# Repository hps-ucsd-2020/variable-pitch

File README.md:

# variable-pitch

This is where code for the variable pitch system goes

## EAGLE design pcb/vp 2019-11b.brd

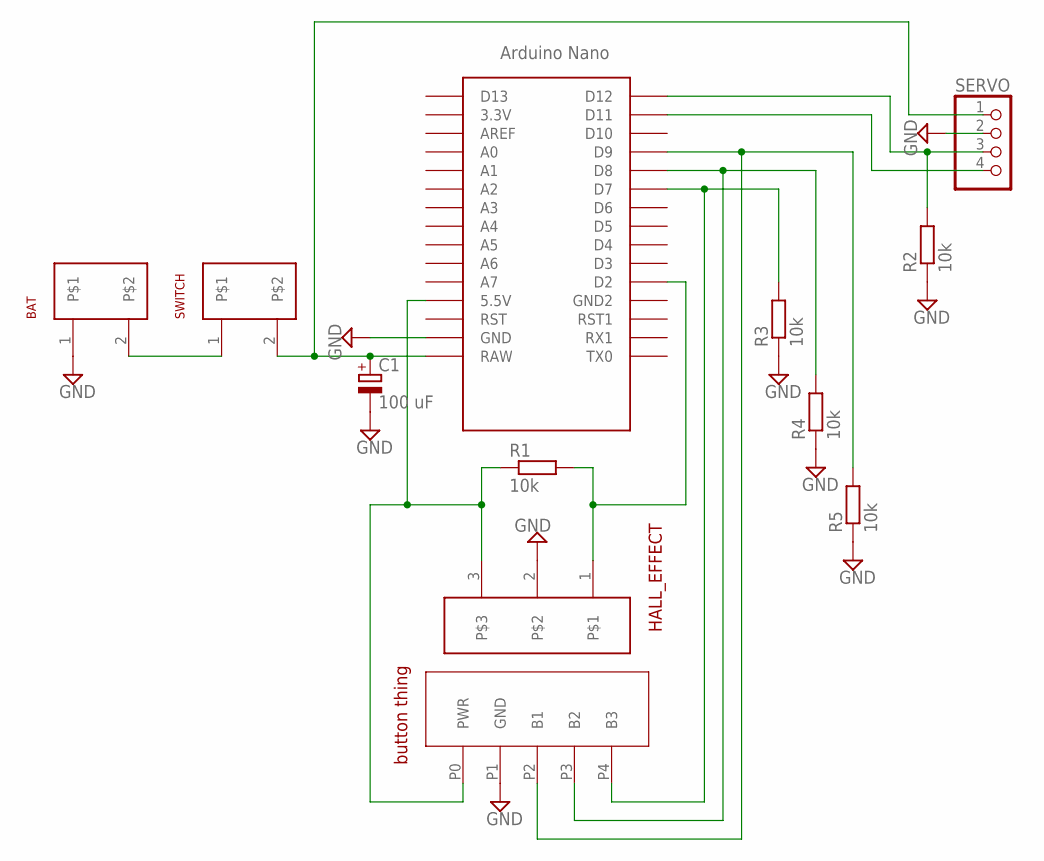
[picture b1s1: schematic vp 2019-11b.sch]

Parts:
BAT: TERMINAL_2POS
BUTTON: BUTTON_CRAP; 5PIN
C1: 100 uF; E2-5
HALL_EFFECT: TERMINAL_3POS
R1, R2, R3, R4, R5: 10k; R0603
SERVO: PINHD-1X4; 1X04
SWITCH: TERMINAL_2POS
U$1: NANO

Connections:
GND: BAT.1, BUTTON.P1 (GND), C1.-, HALL_EFFECT.2, R2.1, R3.1, R4.1, R5.1, SERVO.2, U$1.GND
unnamed: R2.2, SERVO.3, U$1.D12
unnamed: SERVO.4, U$1.D11
unnamed: C1.+, SERVO.1, SWITCH.2, U$1.RAW
unnamed: BUTTON.P0 (PWR), HALL_EFFECT.3, R1.1, U$1.5V (5.5V)
unnamed: BAT.2, SWITCH.1
unnamed: HALL_EFFECT.1, R1.2, U$1.D2
unnamed: BUTTON.P4 (B3), R3.2, U$1.D7
unnamed: BUTTON.P3 (B2), R4.2, U$1.D8
unnamed: BUTTON.P2 (B1), R5.2, U$1.D9

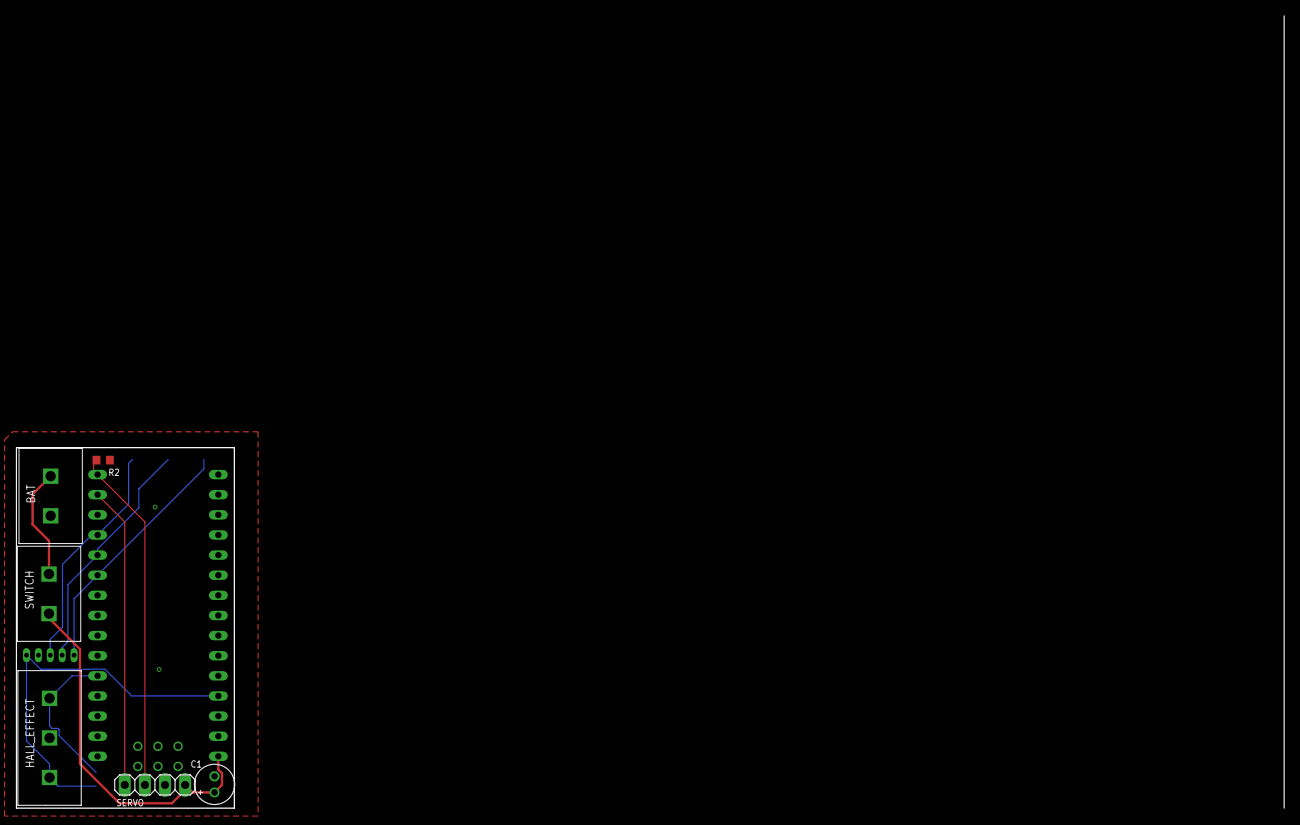
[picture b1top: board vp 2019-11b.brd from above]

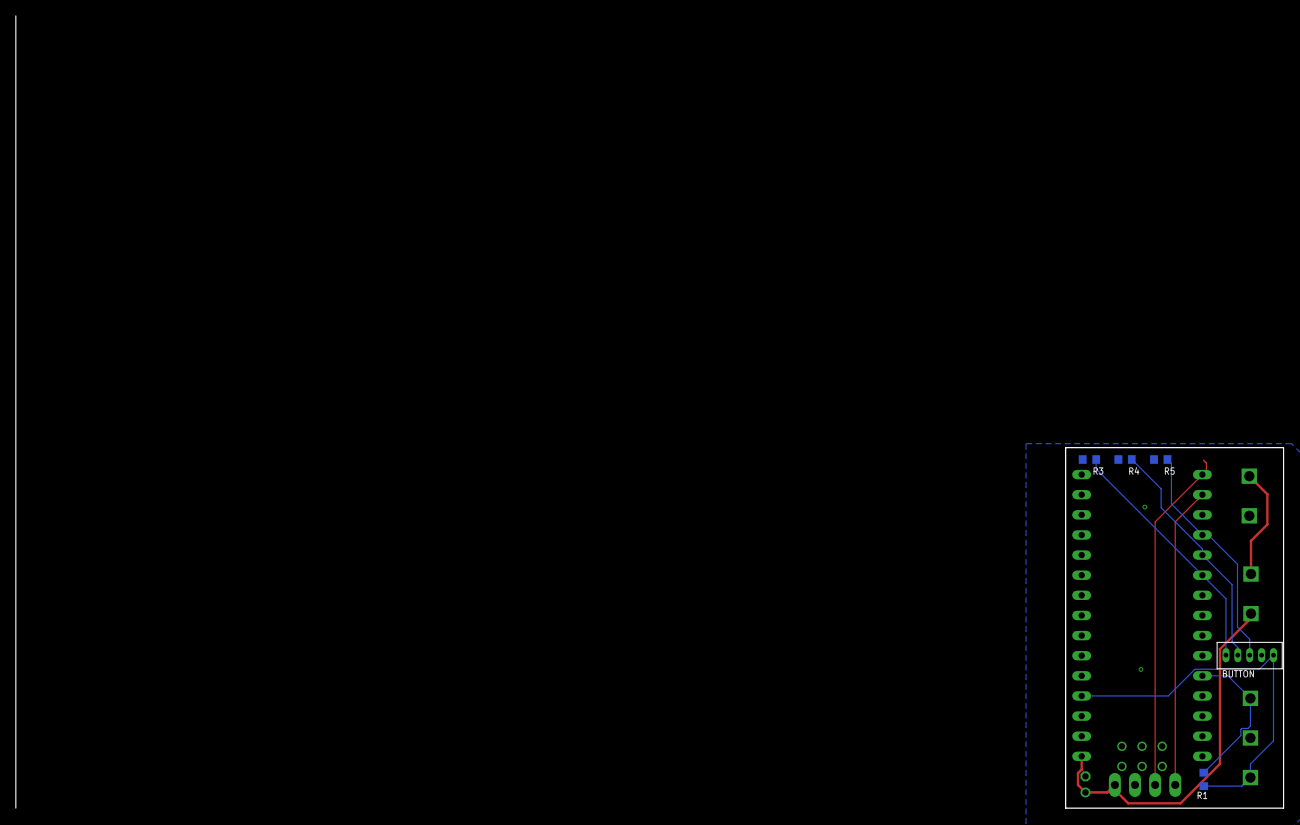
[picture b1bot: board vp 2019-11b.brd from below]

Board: 2 copper layers, 27.5 x 45.5 mm, 12 parts (6 on the bottom side), 10 nets.

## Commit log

2020-02-27 added actual variable pitch code
2020-02-29 added information about PCB and preprocessor directives to change pin assingments
